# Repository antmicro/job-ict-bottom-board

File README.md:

# Jetson Orin Baseboard ICT Bottom Board

Copyright (c) 2025 [Antmicro](https://www.antmicro.com)

## Overview

This project includes PCB design files for a board which allows to perform In-Circuit Testing (ICT) of Antmicro's [Jetson Orin Baseboard](https://github.com/antmicro/jetson-orin-baseboard).
It contains a set of spring-loaded needle probes that connect to the relevant testpoints on the bottom side of the Jetson Orin Baseboard.
This allows to perform In-Circuit driving of DC/DC enable signals and measure the resulting voltages on the board under test. 
The Jetson Orin Baseboard ICT Bottom Board should be used with the [ICT Baseboard](https://github.com/antmicro/ict-baseboard) which performs the actual testing.  

The design files were prepared in KiCad 9.x.

## Key features

* Spring loaded test probes matching the notable testpoints exposed on the [Jetson Orin Baseboard](https://github.com/antmicro/jetson-orin-baseboard)
* Four bi-color (Red/Green) LEDs for status indication
* ESD protection for all IO channels
* Compatible with [ICT Baseboard](https://github.com/antmicro/ict-baseboard)

## Project structure

The main directory contains KiCad PCB project files, a LICENSE, and a README. 
The remaining files are stored in the following directories:

* `img` - contains graphics for this README
* `mechanical` - contains mechanical part in `.step` format

## Licensing

This project is published under the [Apache-2.0](LICENSE) license.

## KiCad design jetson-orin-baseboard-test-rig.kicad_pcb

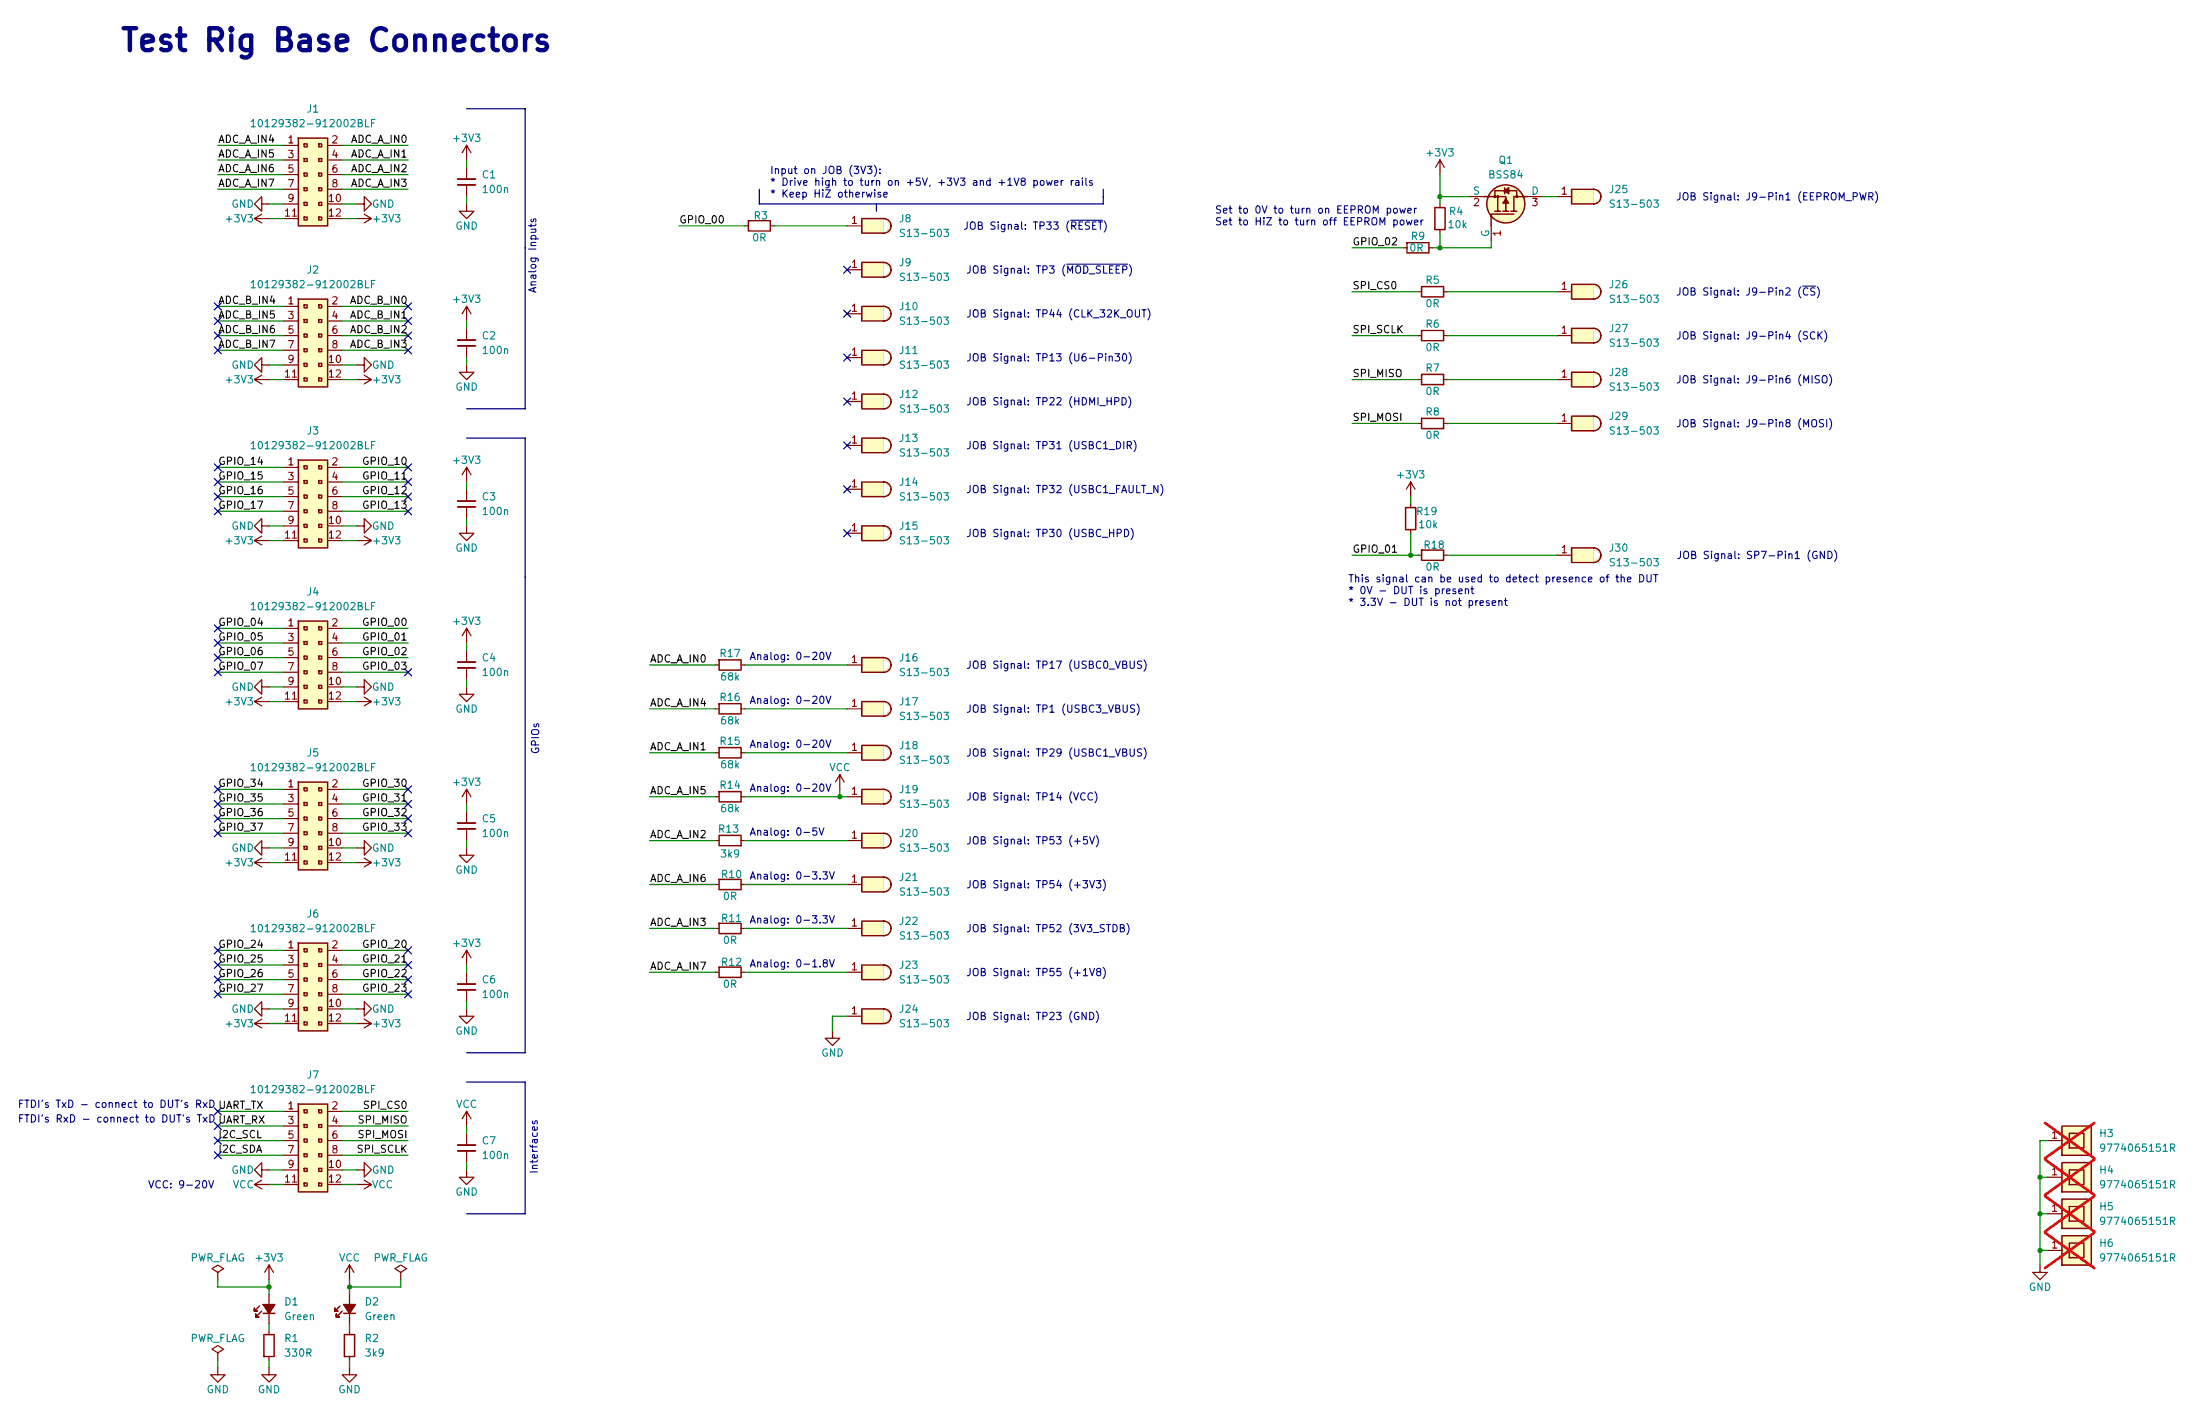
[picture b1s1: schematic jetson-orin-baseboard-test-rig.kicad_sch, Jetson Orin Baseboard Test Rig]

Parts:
C1, C2, C3, C4, C5, C6, C7: C_100n_0402; C_0402_1005Metric; Voltage 50V; MPN GRM155R61H104KE14D
D1, D2: LED_G_0603_KP-1608CGCK; LED_0603_1608Metric_G; MPN KP-1608CGCK
H3, H4, H5, H6: Spacer_Drill3.7mm_H6.5mm_9774065151R; MPN 9774065151R; not fitted
J1, J2, J3, J4, J5, J6, J7: PinHeader_2x6_P2.54mm_Drill1.1mm_Horizontal; MPN 10129382-912002BLF
J8, J9, J10, J11, J12, J13, J14, J15, J16, J17, J18, J19, J20, J21, J22, J23, J24, J25, J26, J27, J28, J29, J30: Harwin_1x1_H17.75mm_Drill0.8mm_S13-503; PogoPin_Harwin_1x1_H17.75mm_Drill0.8mm_S13-503; MPN S13-503
Q1: BSS84; SOT-23-3; MPN BSS84
R1: R_330R_0402; R_0402_1005Metric; Tolerance 1%; MPN CR0402-FX-3300GLF
R2, R13: R_3k9_0402; R_0402_1005Metric; Tolerance 1%; MPN CR0402-FX-3901GLF
R3, R5, R6, R7, R8, R9, R10, R11, R12, R18: R_0R_0402; R_0402_1005Metric; MPN ERJ2GE0R00X
R4, R19: R_10k_0402; R_0402_1005Metric; Tolerance 1%; MPN CR0402-FX-1002GLF
R14, R15, R16, R17: R_68k_0402; R_0402_1005Metric; Tolerance 1%; MPN CR0402-FX-6802GLF

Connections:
+3V3: C1.2, C2.2, C3.2, C4.2, C5.2, C6.2, D1.2 (A), J1.11, J1.12, J2.11, J2.12, J3.11, J3.12, J4.11, J4.12, J5.11, J5.12, J6.11, J6.12, Q1.2 (S), R4.2, R19.2
/ADC_A_IN0: J1.2, R17.1
/ADC_A_IN1: J1.4, R15.1
/ADC_A_IN2: J1.6, R13.2
/ADC_A_IN3: J1.8, R11.1
/ADC_A_IN4: J1.1, R16.1
/ADC_A_IN5: J1.3, R14.1
/ADC_A_IN6: J1.5, R10.1
/ADC_A_IN7: J1.7, R12.1
/ADC_B_IN0: J2.2
/ADC_B_IN1: J2.4
/ADC_B_IN2: J2.6
/ADC_B_IN3: J2.8
/ADC_B_IN4: J2.1
/ADC_B_IN5: J2.3
/ADC_B_IN6: J2.5
/ADC_B_IN7: J2.7
/GPIO_00: J4.2, R3.1
/GPIO_01: J4.4, R18.1, R19.1
/GPIO_02: J4.6, R9.1
/GPIO_03: J4.8
/GPIO_04: J4.1
/GPIO_05: J4.3
/GPIO_06: J4.5
/GPIO_07: J4.7
/GPIO_10: J3.2
/GPIO_11: J3.4
/GPIO_12: J3.6
/GPIO_13: J3.8
/GPIO_14: J3.1
/GPIO_15: J3.3
/GPIO_16: J3.5
/GPIO_17: J3.7
/GPIO_20: J6.2
/GPIO_21: J6.4
/GPIO_22: J6.6
/GPIO_23: J6.8
/GPIO_24: J6.1
/GPIO_25: J6.3
/GPIO_26: J6.5
/GPIO_27: J6.7
/GPIO_30: J5.2
/GPIO_31: J5.4
/GPIO_32: J5.6
/GPIO_33: J5.8
/GPIO_34: J5.1
/GPIO_35: J5.3
/GPIO_36: J5.5
/GPIO_37: J5.7
/I2C_SCL: J7.5
/I2C_SDA: J7.7
/SPI_CS0: J7.2, R5.1
/SPI_MISO: J7.4, R7.1
/SPI_MOSI: J7.6, R8.1
/SPI_SCLK: J7.8, R6.1
/UART_RX: J7.3
/UART_TX: J7.1
GND: C1.1, C2.1, C3.1, C4.1, C5.1, C6.1, C7.1, H3.1, H4.1, H5.1, H6.1, J1.9, J1.10, J2.9, J2.10, J3.9, J3.10, J4.9, J4.10, J5.9, J5.10, J6.9, J6.10, J7.9, J7.10, J24.1, R1.1, R2.1
unnamed: D1.1 (C), R1.2
unnamed: D2.1 (C), R2.2
unnamed: J8.1, R3.2
unnamed: J16.1, R17.2
unnamed: J17.1, R16.2
unnamed: J18.1, R15.2
unnamed: J20.1, R13.1
unnamed: J21.1, R10.2
unnamed: J22.1, R11.2
unnamed: J23.1, R12.2
unnamed: J26.1, R5.2
unnamed: J27.1, R6.2
unnamed: J28.1, R7.2
unnamed: J29.1, R8.2
unnamed: J30.1, R18.2
unnamed: J25.1, Q1.3 (D)
unnamed: Q1.1 (G), R4.1, R9.2
VCC: C7.2, D2.2 (A), J7.11, J7.12, J19.1, R14.2

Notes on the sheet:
JOB Signal: J9-Pin6 (MISO)
JOB Signal: TP23 (GND)
JOB Signal: TP1 (USBC3_VBUS)
JOB Signal: TP14 (VCC)
Analog: 0-3.3V
JOB Signal: J9-Pin8 (MOSI)
JOB Signal: TP3 (~{MOD_SLEEP})
VCC: 9-20V
This signal can be used to detect presence of the DUT * 0V - DUT is present * 3.3V - DUT is not present
JOB Signal: TP44 (CLK_32K_OUT)
JOB Signal: J9-Pin1 (EEPROM_PWR)
JOB Signal: TP32 (USBC1_FAULT_N)
Analog: 0-20V
JOB Signal: TP29 (USBC1_VBUS)
JOB Signal: TP17 (USBC0_VBUS)
JOB Signal: TP53 (+5V)
JOB Signal: TP13 (U6-Pin30)
Test Rig Base Connectors
FTDI's TxD - connect to DUT's RxD
JOB Signal: SP7-Pin1 (GND)
Analog: 0-1.8V
Interfaces
JOB Signal: J9-Pin4 (SCK)
Input on JOB (3V3): * Drive high to turn on +5V, +3V3 and +1V8 power rails * Keep HiZ otherwise
JOB Signal: TP31 (USBC1_DIR)
Analog: 0-5V
JOB Signal: TP54 (+3V3)
JOB Signal: TP22 (HDMI_HPD)
JOB Signal: TP30 (USBC_HPD)
JOB Signal: TP52 (3V3_STDB)
JOB Signal: TP55 (+1V8)
JOB Signal: J9-Pin2 (~{CS})
GPIOs
JOB Signal: TP33 (~{RESET})
Set to 0V to turn on EEPROM power Set to HiZ to turn off EEPROM power
FTDI's RxD - connect to DUT's TxD
Analog Inputs

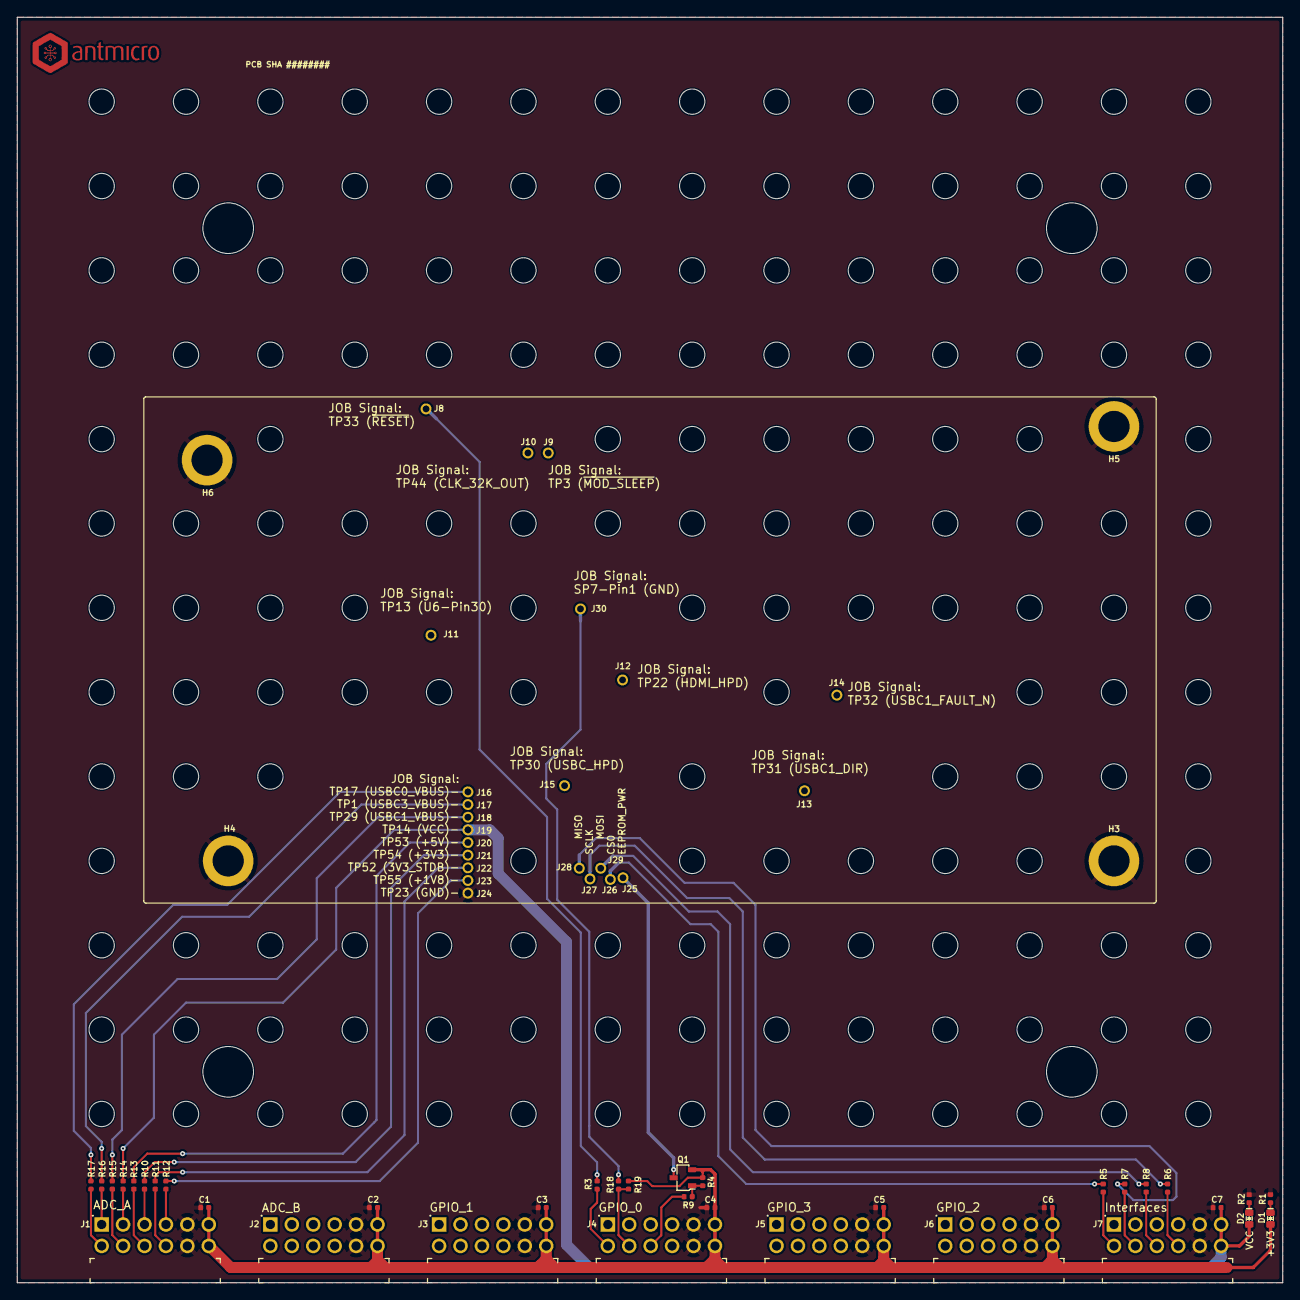
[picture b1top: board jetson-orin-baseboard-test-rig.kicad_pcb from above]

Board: 2 copper layers, 150.0 x 150.0 mm, 63 parts (0 on the bottom side), 35 nets.

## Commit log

2025-05-15 [#77400] Initial commit
2025-05-15 [#77400] Prepare initial mechanic outline
2025-05-15 [#77400] Add spring probes (WiP)
2025-05-16 [#77400] Finalize schematic
2025-05-16 [#77400] Clean ERC
2025-05-16 [#77400] Add .ci.yml
2025-05-16 [#77400] Finish routing
2025-05-16 [#77400] Update date, update logos
2025-05-16 [#77400] Add LEDs
2025-05-26 [#77400] Add grounded mounting pad
2025-05-27 [#77400] Add TVS
2025-05-27 [77400] Add studs
2025-05-27 [#77400] Update holes
2025-05-27 [#77400] Update mounting studs
2025-06-25 [#79468] Save with KiCad9
2025-06-25 [#79468] Import sheet naming changes from KiCad9
2025-06-25 [#79468] Bump rev to 1.1.0
2025-06-25 [#79468] Add I2C pins to SCH
2025-06-25 [#79468] Position pins on the PCB
2025-06-25 [#79468] Convert DRCs to KiCad9
2025-06-25 [#79468] Route connections
2025-06-25 [#79468] Resolve DRCs
2025-06-25 [#79468] Update Pogo Pins from Lib
2025-06-25 [#79468] Space apart the I2C2 pins
2025-06-26 [#79468] Improve silk
2025-06-26 [#79468] Cleanup ERC & DRC
2025-06-26 [#79468] Update LED resistors
2025-06-26 [#79468] Update silk
2025-06-30 [#79468] Remove unconnected mark
2025-06-30 [#79620] Add README
2025-06-30 [#79620] Update ci.yml
2025-06-30 [#79620] Update README header
2025-07-01 [#79620] Rename to JOB ICT Bottom Board, Bump rev to 1.1.1
2025-07-01 [#79620] README review
2025-07-01 [#79620] Update README naming
2025-07-01 [#79620] Add render
2025-07-01 [#79620] link render in the README
2025-07-03 [#79620] Mark NPTH holes as not in the schematics
2025-07-03 [#79620] Remove leftover assembly drawings
2025-07-03 [#79620] Update stackup
2025-07-03 [#79620] Sync DNP settings
2025-07-04 Add OHP badge
2025-07-04 Add mechanical parts
2025-07-07 README updates
2025-07-07 README: update render
2025-07-07 README: fix
2025-08-06 Update mechanical models name
2025-08-18 Add blendcfg

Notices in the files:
parts and their libraries:
License: Apache-2.0
